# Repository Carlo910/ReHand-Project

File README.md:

# AY2223_I_Project-3

Re-Hand Versione 1.0 13/02/2023

***
Short Description:

Re-Hand is a device that uses 4 flex sensors, mounted on a glove, to recognize gestures. It is designed to be used in rehabilitation, to train subjects who experience problems in perfoming the "grasping" movement. Rehabilitation is done through repetition of the "grasping" gesture by playing a game by carrying out precise instructions given on the screen.
Breve descrizione:

Itlian version: 
Re-Hand è un dispositivo che utilizza 4 flex sensors, montati su di un guanto, per riconoscere dei gesti. 
E' stato pensato per essere utilizzato in ambito riabilitativo, per allenare soggetti che riscontrano problemi nel perfomare il
movimento del "grasping". 
La riabilitazione viene effettuata tramite la ripetizione del gesto del "grasping" svolgendo un gioco eseguendo precise istruzioni fornite a schermo. 

***

Hardware:

A glove is used on which four flex sensors, from thumb to ring finger, are sewn onto the top of the fingers. To read the value measured by the sensors, four voltage dividers (one for each sensor) were made with four 2 kOhm resistors. A PSoC 5LP Dev Kit CY8CKIT-059 was used as the microcontroller. The device was designed as a wearable, so it is equipped with a bluetooth module for sensor data communication and a 3.7 V lipo battery for power supply, with an attached charging circuit.  A 3.3 V linear stabilizer was added to provide the microcontroller with a stabilized voltage, while the Bluetooth gets an unstabilized voltage since the minimum voltage required to power it is 3.6 V.
To check the battery charge level, two identical 1 kOhm resistors were added to read the drop voltage across them.
After prototyping the device, a PCB was made into which all components were soldered. See the 'Eagle' folder to view the model made for printing the PCB.  A case was made thanks to a 3D printer to contain all the hardware components (apart from the sensors and glove). In the 'SolidWorks' folder you can find the model made for printing. It is possible to conveniently turn the device on and off by pressing a switch on the top side of the case. To monitor the bluetooth connection, the user can refer to a red LED located on the side of the case, which flashes at a frequency of 0.2 Hz during bluetooth connection and turns solid once the connection is successfully occurred.

***
PsoC Creator 
The Psoc Creator IDE (Integrated Design Environment) was used to develop the project from the firmware side. 
Within the 'PSOC' folder can be found the 'Project3' workspace which contains the 'Project3' project where the code used to sample the data, average it and finally send it via Bluetooth to the connected device. 
For data sampling, the frequency of the interrupt timer was set to 10 Hz. Once a piece of data is received, it waits to have 10 samples in order to average them and then send them. In addition, every minute the
the battery charge value and then sent. Also managed within the code is the Bluetooth connection and its Led to display whether it has taken place (Led on) or not (Led flashes at 0.2 Hz). In addition, there is the project 'Project3_dataset' which was used to build the datasets for the development of the classifier. A different code is used to make data collection easier by simplifying the connection with the  device that receives the data.

***

Python

To use Re-Hand you need version 3.9 with various libraries to install on your virtual enviroment.
See the file 'requirements.txt' in the folder and run it in your virtual  
environment to install all the required libraries with their respective versions.
 
Upon launching the GUI.py code, the name of the Re-Hand project appears on the screen and the user will be asked to enter their name, thanks to which it will be possible to save performance data from different users. Next, the user can click  a start button, which allows the start of sampling the values of the four variable resistors. In case the user has not entered the name, he/she will not be able to access the second screen and an error message will be displayed on asscreen. Once the start button is pressed, a new screen is opened where the user can choose whether to play the game, or display on the screen some statistical data on the improvement in playing it. 

Thanks to a classifier, specifically a Random Forest, the device can recognize six gestures in total, three used to move through the different GUI windows and three for the rehabilitation task. In the file 'classification_6gestures.ipynb' it is possible to see how the model used for the classification of the gestures. The files 'dataset_training_6gesti.csv' and 'dataset_test_6gesti.csv' contain all the data used to
train and test the model which were collected using the code 'code_dataset.py'. In the file 'rf_model_6gesti.pkl' is saved the model trained on the datasets mentioned above and used to perform real-time prediction for gesture recognition while using the application.

By raising only the index finger (target 4), one enters the game window. At this point the user can start performing the gesture
of grasping, starting with the hand fully open (target 0), then trying to close it halfway (target 1) and finally closing the fist completely (target 2). While performing these gestures, the user will be able to see on the screen an image of a bow being drawn, progressively as the hand closes, until an arrow is fired. Once the game is finished, the time it took the user to complete the gesture is printed on the screen. In the event that the exercise is not performed correctly (time taken longer than 30 seconds) a message will be displayed on the screen a message inviting the user to exit the game and try again. By raising only the thumb while keeping the hand closed (target 3), you will exit the game screen and return to the main Home screen. 

At this point, by raising both index and average (target 5) you can enter the statistics screen, where a graph can be displayed on the screen showing the times in seconds in which the user has done the last ten exercises, if any, with the respective date so that any improvements can be visualized. The display of statistics is allowed only if the user has completed the game at least twice, otherwise an error message appears on the screen. The following graph also shows failed attempts by reporting a time of 30 seconds (the maximum attainable value), highlighted on the graph by a red line. The user's best result, absolute worst result (in case of success) and the number of failed attempts are also displayed. By raising only the thumb while keeping the hand closed (target 3), you exit the game screen to return to the main Home screen. 

***

Italian version:

Hardware:
Si utilizza un guanto su cui sono cuciti quattro flex sensors, dal pollice all'anulare, sulla parte superiore delle dita. Per leggere
il valore misurato dai sensori sono stati realizzati 4 partitori di tensione (uno per ogni sensore) con 4 resistenze da 2 kOhm.
Come microcontrollore è stato usato un PSoC 5LP Dev Kit CY8CKIT‐059.  
Il device è stato pensato come wearble, per cui è dotato di modulo bluetooth per la comunicazione dei dati dei sensori e di una batteria lipo a 3.7 V per
l'alimentazione, con annesso circuito di ricarica. 
E' stato aggiunto uno stabilizzatore lineare a 3.3 V per fornire al microcontrollore una tensione stabilizzata, mentre al modulo
bluetooth arriva una tensione non stabilizzata poichè la minima tensione richiesta per alimentarlo è di 3.6 V.
Per controllare il livello di carica della batteria sono state aggiunte due resistenze identiche da 1 kOhm per leggere la caduta
di tensione su di esse.
Dopo aver realizzato il dispositivo in via prototipale è stata realizzata una PCB in cui sono stati saldati tutti i componenti.
Vedere la cartella 'Eagle' per visualizzare il modello realizzato per la stampa della PCB. 
Per contenere tutti i componenti hardware (a parte i sensori e guanto) è stato realizzato un case grazie ad una stampante 3D. Nella
cartella 'SolidWorks' è possibile trovare la realizzazione del modello per la stampa.
E' possibile accendere e spegnere comodamente il dispositivo premendo un interruttore posto sul lato superiore del case.
Per monitorare la connessione del bluetooth, l'utente può fare riferimento a un led rosso posizionato lateralmente al case, il quale
lampeggia a una frequenza di 0,2 Hz durante la connessione del bluetooth e diventa fisso una volta che la connessione è correttamente
avvenuta.

***

PsoC Creator 
E' stato utilizzato il Psoc Creator IDE (Integrated Design Environment) per sviluppare il progetto dal lato firmware. 
All'interno della cartella 'PSOC' si può trovare il workspace 'Project3' il quale contiene il progetto 'Project3' dove si trova il 
codice utilizzato per campionare i dati, mediarli e infine inviarli tramite Bluetooth al dispositivo connesso. 
Per il campionamento dei dati è stata impostata la frequenza del timer dell'interrupt a 10 Hz. Una volta ricevuto un dato si attende
di avere 10 campioni per poter calcolare la media di questi ultimi e successivamente inviarli. In aggiunta ogni minuto viene misurato
il valore di carica della batteria e poi inviato.
All'interno del codice è gestita anche la connessione del Bluetooth e il relativo Led per visualizzare se è avvenuta (Led acceso)
oppure no (Led lampeggia a 0,2 Hz).
Inoltre è presente il progetto 'Project3_dataset' il quale è stato usato per la realizzazione dei dataset per lo sviluppo del 
classificatore. Viene usato un codice diverso per rendere la raccolta dei dati più agevole semplificando la connessione con il 
dispositivo che riceve i dati.

***

Python

Per utilizzare Re-Hand è necessaria la versione 3.9 con varie librerie da installare sul prorpio virtual enviroment.
Vedere nella cartella il file 'requirements.txt' e eseguirlo nel prorpio virtual  
environment per installare tutte le librerie necessarie con le rispettive versioni.
 
Lanciando il codice GUI.py appare a schermo il nome del progetto Re-Hand e verrà chiesto all'utente di inserire il proprio 
nome, grazie al quale sarà possibile salvare i dati delle prestazioni di diversi utenti. In seguito l'utente può cliccare 
un pulsante di start, che permette l'inizio del campionamento dei valori delle quattro resistenze variabili.
Nel caso in cui l'utente non abbia inserito il nome, non potrà accedere alla seconda schermata e verrà visualizzato a aschermo un messaggio di errore.
Una volta premuto il pulsante di start, viene aperta una nuova schermata dove l'utente può scegliere se svolgere il gioco, 
oppure visualizzare a schermo alcuni dati statistici sul miglioramento nello svolgimento dello stesso.

Grazie a un classificatore, in particolare un Random Forest, il dispositivo riesce a riconoscere sei gesti in totale,
tre utilizzati per muoversi attraverso le diverse finestre della GUI e tre per l'attività di riabilitazione.
Nel file 'classification_6gesti.ipynb' è possibile visualizzare come è stato realizzato il modello usato per la
classificatione dei gesti. I files 'dataset_training_6gesti.csv' e 'dataset_test_6gesti.csv' contengono tutti i dati usati per
allenare e testare il modello i quali sono stati raccolti utilizzando il codice 'codice_dataset.py'. Nel file 'rf_model_6gesti.pkl' è
salvato il modello allenato sui dataset citati sopra e usato per compiere la predizione i tempo reale per il riconoscimento dei gesti
durante l'utilizzo dell'applicazione.

Alzando solo l'indice (target 4), si entra nella finestra del gioco. A questo punto l'utente può iniziare a performare il gesto
del grasping, partendo con la mano completamente aperta (target 0), provando poi a chiuderla a metà (target 1) e infine
chiudendo completamente il pugno (target 2). Durante l'esecuzione di questi gesti, l'utente potrà visualizzare a schermo
l'immagine di un arco che viene tirato, progressivamente alla chiusura della mano, fino a scoccare una freccia. 
Una volta finito il gioco viene stampato a schermo il tempo che l'utente ha impiegato per completare il gesto.
Nel caso in cui l'esercizio non venga svolto correttamente (tempo di svolgimento superiore a 30 secondi) verrà visualizzato 
a schermo un messaggio che inviterà l'utente a uscire dal gioco e a riprovare. Alzano solo il pollice mantenendo la mano chiusa
(target 3), si esce dalla schermata del gioco per tornare nella schermata Home principale. 
 
A questo punto, alzando sia indice che medio (target 5) è possibile entrare nella schermata delle statistiche,
dove si può visualizzare a schermo un grafico che mostra i tempi in secondi in cui l'utente ha svolto gli ultimi dieci l'esercizi, se presenti, con la rispettiva
data in modo da poter visualizzare gli eventuali miglioramenti. La visualizzazione delle statistiche viene permessa solo se
l'utente ha completato almeno due volte il gioco, in caso contrario appare a schermo un messaggio di errore.
Il seguente grafico inoltre mostra anche i tentativi falliti riportando un tempo di 30 secondi (il massimo valore raggiungibile),
evidenziato sul grafico da una linea rossa.
Vengono inoltre visualizzati il risultato migliore, quello peggiore in assoluto dell'utente (in caso di successo) e il numero di tentativi falliti.
Alzano solo il pollice mantenendo la mano chiusa
(target 3), si esce dalla schermata del gioco per tornare nella schermata Home principale.

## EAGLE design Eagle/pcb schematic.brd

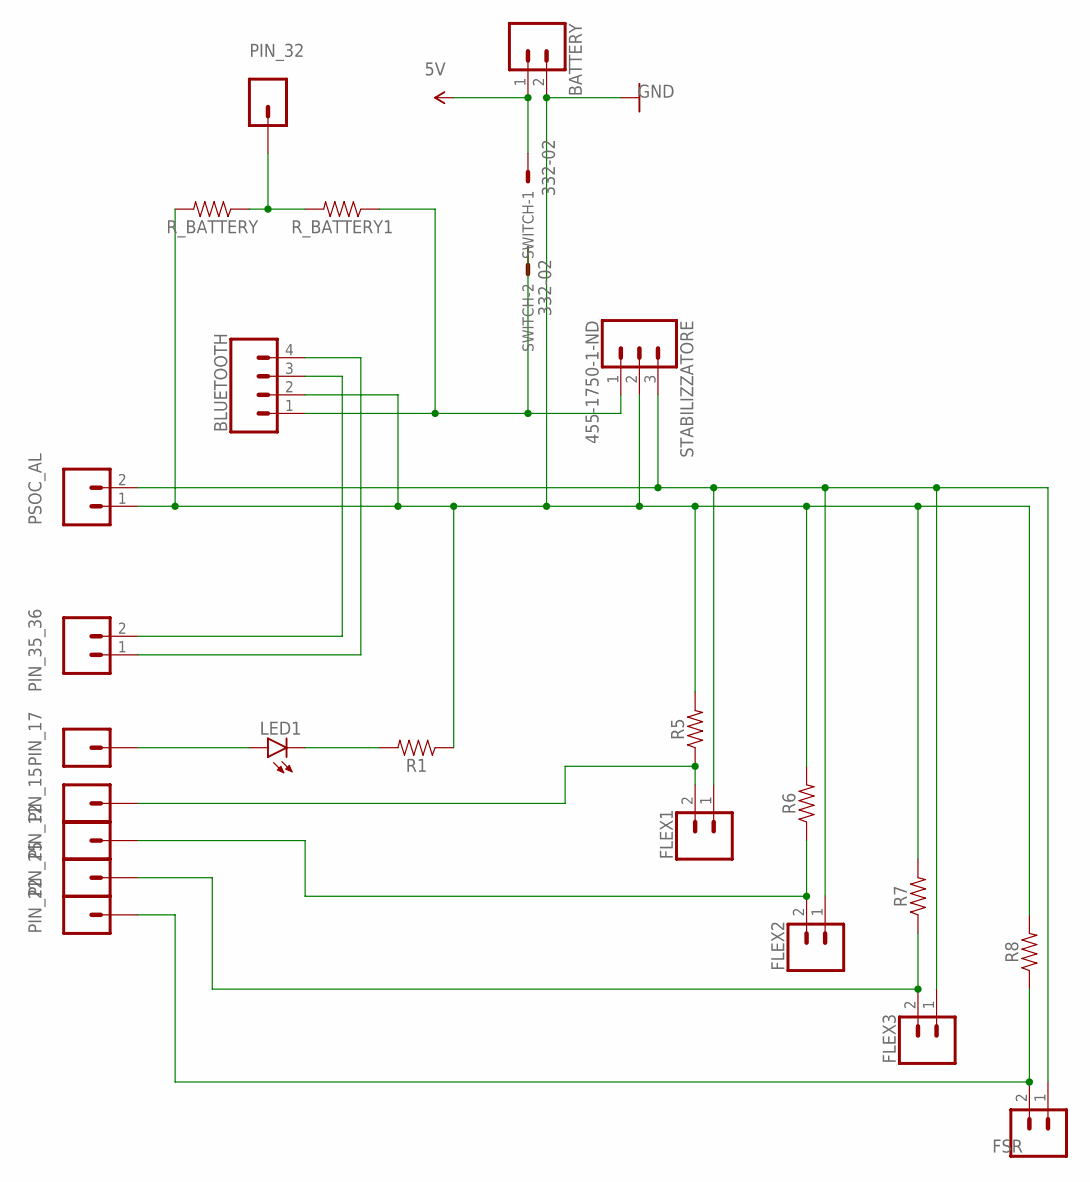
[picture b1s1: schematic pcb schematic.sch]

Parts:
BATTERY: CONN_02; 1X02
BLUETOOTH: CONN_04; 1X04
FLEX1, FLEX2, FLEX3: CONN_02; 1X02
FSR: CONN_02; 1X02
LED1: LED5MM
PIN_12, PIN_15, PIN_17, PIN_22, PIN_25, PIN_32: CONN_01; 1X01
PIN_35_36: CONN_02; 1X02
PSOC_AL: CONN_02; 1X02
R1, R5, R6, R7, R8: AXIAL-0.3
R_BATTERY, R_BATTERY1: AXIAL-0.3
STABILIZZATORE: 455-1750-1-ND; 1X03
SWITCH: 332-02

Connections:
5V: BATTERY.1, SWITCH.1
GND: BATTERY.2, BLUETOOTH.2, PSOC_AL.1, R1.P$1 (1), R5.P$2 (2), R6.P$2 (2), R7.P$2 (2), R8.P$2 (2), R_BATTERY.P$2 (2), STABILIZZATORE.2
unnamed: FLEX1.2, PIN_15.1, R5.P$1 (1)
unnamed: FLEX2.2, PIN_12.1, R6.P$1 (1)
unnamed: FLEX3.2, PIN_25.1, R7.P$1 (1)
unnamed: BLUETOOTH.3, PIN_35_36.2
unnamed: FSR.2, PIN_22.1, R8.P$1 (1)
unnamed: BLUETOOTH.4, PIN_35_36.1
unnamed: LED1.A, PIN_17.1
unnamed: LED1.K (C), R1.P$2 (2)
unnamed: PIN_32.1, R_BATTERY.P$1 (1), R_BATTERY1.P$2 (2)
unnamed: BLUETOOTH.1, R_BATTERY1.P$1 (1), STABILIZZATORE.1, SWITCH.2
unnamed: FLEX1.1, FLEX2.1, FLEX3.1, FSR.1, PSOC_AL.2, STABILIZZATORE.3

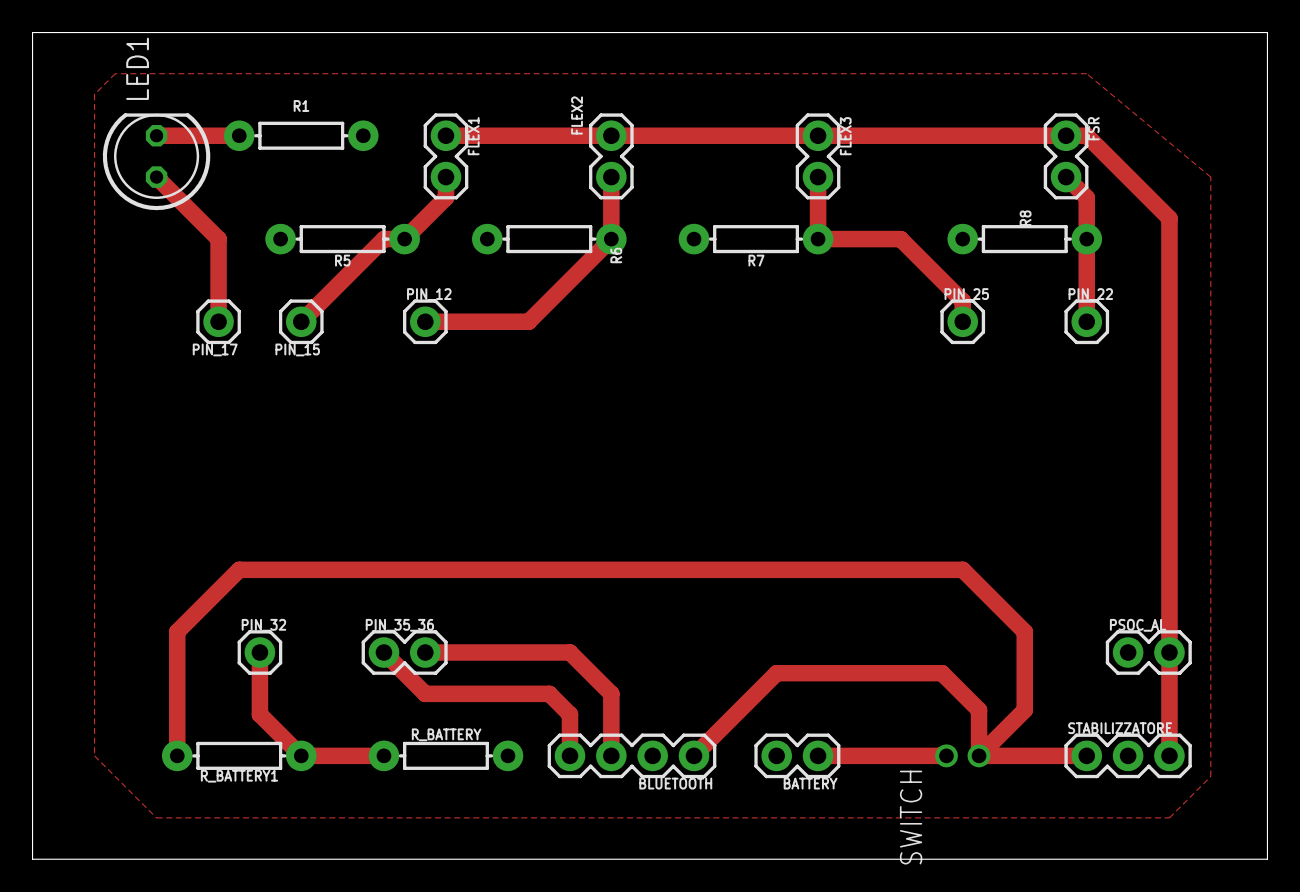
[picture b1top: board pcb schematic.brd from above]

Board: 2 copper layers, 75.9 x 50.8 mm, 24 parts (1 on the bottom side), 13 nets.

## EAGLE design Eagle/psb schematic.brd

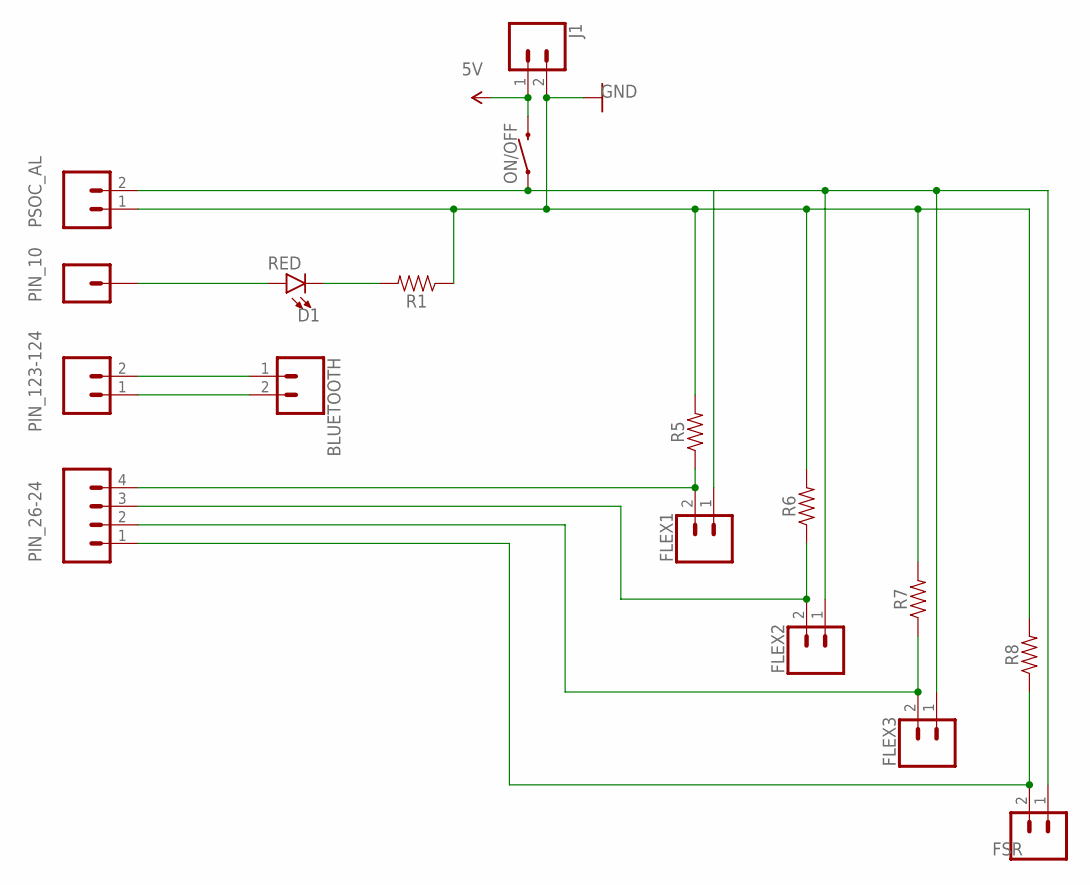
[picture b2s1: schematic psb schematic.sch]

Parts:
BLUETOOTH: CONN_02; 1X02
D1: RED; LED-0603
FLEX1, FLEX2, FLEX3: CONN_02; 1X02
FSR: CONN_02; 1X02
J1: CONN_02; 1X02
ON/OFF: MOMENTARY-SWITCH-SPST-SMD-6.0X3.5MM; TACTILE_SWITCH_SMD_6.0X3.5MM
PIN_10: CONN_01; 1X01
PIN_26-24: CONN_04; 1X04
PIN_123-124: CONN_02; 1X02
PSOC_AL: CONN_02; 1X02
R1, R5, R6, R7, R8: AXIAL-0.3

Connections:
5V: J1.1, ON/OFF.2
GND: J1.2, PSOC_AL.1, R1.P$1 (1), R5.P$2 (2), R6.P$2 (2), R7.P$2 (2), R8.P$2 (2)
unnamed: FLEX1.2, PIN_26-24.4, R5.P$1 (1)
unnamed: FLEX2.2, PIN_26-24.3, R6.P$1 (1)
unnamed: FLEX3.2, PIN_26-24.2, R7.P$1 (1)
unnamed: BLUETOOTH.1, PIN_123-124.2
unnamed: FSR.2, PIN_26-24.1, R8.P$1 (1)
unnamed: BLUETOOTH.2, PIN_123-124.1
unnamed: FLEX1.1, FLEX2.1, FLEX3.1, FSR.1, ON/OFF.1, PSOC_AL.2
unnamed: D1.A, PIN_10.1
unnamed: D1.C, R1.P$2 (2)

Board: 2 copper layers, 17 parts (0 on the bottom side), 11 nets, no tracks yet.

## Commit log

2022-11-16 first
2022-11-16 da PutString a PutArray per invio corretto dei dati
2022-11-21 Prima versione media tra dieci campioni
2022-11-21 Lettura di tutti i sensori per determinare la threshold
2022-11-21 creazione cartella PSOC
2022-11-21 Ordine cartella
2022-11-21 Inizio PCB
2022-11-21 Aggiunto gitignore Eagle
2022-11-21 aggiunta gitignore per eagle
2022-11-23 Prima versione python code
2022-11-23 modifica codice Psoc e Python
2022-11-23 prova gestione dati da PSOC, da cambiare e fare su Python
2022-11-28 codice di lettura con menu per la scelta della porta seriale
2022-11-28 modifica file psoc
2022-11-28 Correzioni PCB
2022-11-28 PCB finita
2022-11-28 lettura dati senza ricostruzione pacchetto
2022-11-28 lettura di 10 bytes
2022-11-28 lettura pacchetto
2022-11-30 Prova controllo packets
2022-11-30 ordine dei sensori
2022-11-30 tentativo di combinare i codici
2022-11-30 Controllo gesto prova
2022-11-30 riconoscimento primo gesto
2022-11-30 prova funzionamento
2022-11-30 Aggiunta grafico dati
2022-11-30 pulizia file python iniziali
2022-11-30 Aggiunta bluetooth e passaggio valori attraverso i thread
2022-12-02 PCB modifica tracce e aggiunta componenti batteria
2022-12-02 PCB con pin separati senza errori
2022-12-04 Creato folder per il case e inizio progettazione
2022-12-04 Correzioni psoc
2022-12-04 Nuovo codice per la creazione del dataset
2022-12-06 Correzione bluetooth Psoc
2022-12-06 prima prova dataset
2022-12-07 rete neurale con dataset per il training e per il test
2022-12-07 Inizio grafica, primo pulsante e campionamento
2022-12-09 aggiunta di altra finestra, pulsanti quadrati
2022-12-13 Due finistre, con ricezione del pacchetto nella seconda finestra
2022-12-16 Case quasi finito. Mancano alcuni fori.
2022-12-16 Nuovo codice per la grafica
2022-12-16 inizio modello per la classificazione
2022-12-16 sistemare training modello
2022-12-16 Definizione modello classificazione
2022-12-16 prove modello
2022-12-16 prime 3 finestre con controllo delle dita
2022-12-18 modifica handle_packet
2022-12-19 Nuova rete per classificazione gesti
2022-12-19 case finito + modifica pcb
2022-12-19 Modifica pcb + case finito
2022-12-19 Creazione dataset più grande e training, salvataggio e predizione con modello salvato
2022-12-20 Implementato random forest e prova LSTM
2022-12-20 pulsanti con scritte e quarta schermata
2022-12-20 scritte con font più grande
2022-12-29 nuovo dataset con pollice in posizione correttae rete modificata per meno dati
2022-12-30 test set con pollice alzato
2023-01-05 immagini per i pulsanti e inizio del gioco
2023-01-05 Inizio grafico statistiche
2023-01-09 RF con dataset nuovo
2023-01-09 aggiunta shuffle dati e salvataggio modello RF
2023-01-10 prova con bluetooth nuovo
2023-01-11 codice del psoc modificato con l'introduzione del LED e modifiche nel codice python
2023-01-19 aggiunta lettura carica batteria
2023-01-19 PCB con aggiunta resistenze per carica batteria
2023-01-19 problemi Led connessione
2023-01-23 Modifica psoc led lampeggia, calcolo batteria modificato, nuove immagini
2023-01-23 immagini senza sfondo
2023-01-24 aggiunta modello nel codice python
2023-01-26 Avanzamento e modifiche gioco
2023-01-27 aggiunta modello per predizione in tempo reale
2023-01-29 aggiunta dataset con gesto 1 e 2 e aggiunto a iniziogui
2023-02-01 modifica case solidworks, mancano solo i fori per le viti
2023-02-02 nuovo layout
2023-02-03 Modifica modello classificazione
2023-02-03 Nuova grafica, introduzione delle tempistiche di esecuzione e del pulsante di uscita
2023-02-04 Icone per la batteria e aggiornamento layout del gioco
2023-02-06 inizio istogramma statistiche
2023-02-07 Introduzione statistiche e rigistro dato
2023-02-08 modifica grafico statistiche, rimangono problemi con le date
2023-02-09 modello nuovo
2023-02-09 aggiunta modello con gesto pollice
2023-02-10 Grafico finito
2023-02-11 tempo migliore e peggiore
2023-02-11 modelli separati gioco e scelte e modello unico, funziona il modello unico
2023-02-12 modifica layout, tempi, staristiche, utente
2023-02-12 aggiunta README.txt
2023-02-12 requirements.txt
2023-02-12 Aggiunta requirements.txt
2023-02-12 GUI con aggiunta di messaggi di errore e icona della batteria in tutte le schermate
2023-02-13 Aggiunta delle ultime modifiche apportate al codice.
2023-02-13 Codici commentato, ultime modifiche python con commenti
2023-02-17 Presentazione in formato pptx e pdf
2024-03-18 Update README.md
    ReadMe in English

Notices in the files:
parts and their libraries:
SparkFun-Connectors: Licensing: Creative Commons ShareAlike 4.0 International - https://creativecommons.org/licenses/by-sa/4.0
